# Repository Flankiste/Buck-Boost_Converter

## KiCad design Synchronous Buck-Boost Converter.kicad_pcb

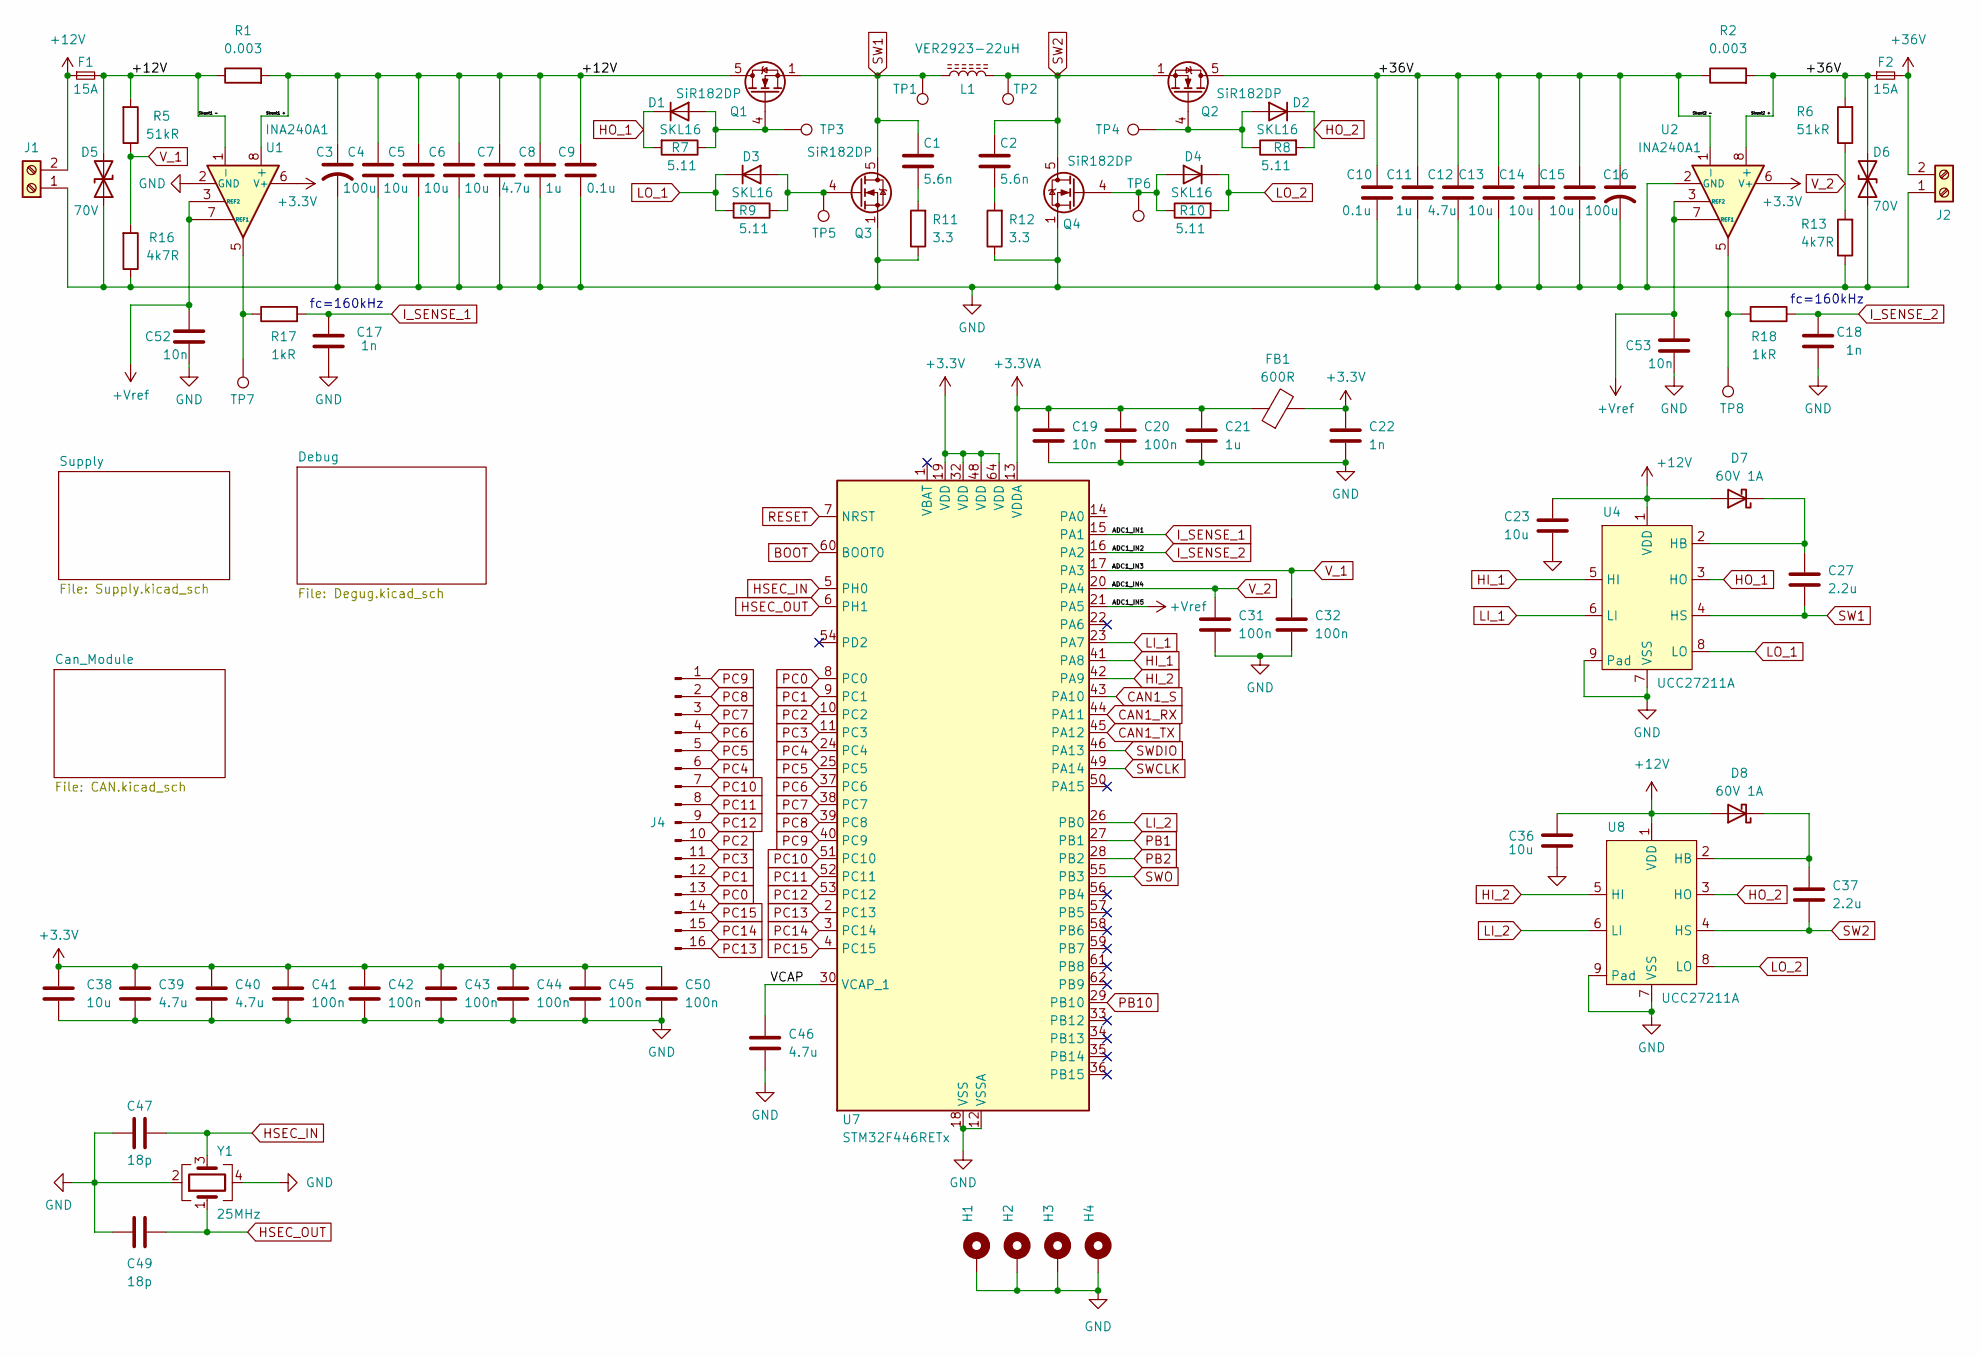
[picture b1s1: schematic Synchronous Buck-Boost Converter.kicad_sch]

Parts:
C1, C2: 5.6n; C_1206_3216Metric
C3, C16: 100u; C_Elec_10x10.2
C4, C5, C6, C13, C14, C15, C23, C36, C38: 10u; C_1210_3225Metric
C7, C12: 4.7u; C_1210_3225Metric
C8, C11: 1u; C_1206_3216Metric
C9, C10: 0.1u; C_0603_1608Metric
C17, C18, C22: 1n; C_0603_1608Metric
C19, C52, C53: 10n; C_0603_1608Metric
C20, C31, C32, C41, C42, C43, C44, C45, C50: 100n; C_0805_2012Metric
C21: 1u; C_0805_2012Metric
C27, C37: 2.2u; C_0805_2012Metric
C39, C40, C46: 4.7u; C_0805_2012Metric
C47, C49: 18p; C_0402_1005Metric
D1, D2, D3, D4: SKL16; Nexperia_CFP3_SOD-123W
D5, D6: 70V; D_SMA
D7, D8: 60V 1A; D_MicroSMP_AK
F1, F2: 15A; Fuse_2512_6332Metric_Pad1.52x3.35mm_HandSolder
FB1: 600R; L_0603_1608Metric
H1, H2, H3, H4: MountingHole_Pad; MountingHole_4.3mm_M4_Pad_Via
J1, J2: Screw_Terminal_01x02; TerminalBlock_Phoenix_MKDS-1,5-2-5.08_1x02_P5.08mm_Horizont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
J4: Conn_01x16_Pin; PinHeader_1x16_P2.54mm_Vertical
L1: VER2923-22uH; VER2923
Q1, Q2, Q3, Q4: SiR182DP; PowerPAK_SO-8_Single
R1, R2: 0.003; R_2512_6332Metric
R5, R6: 51kR; R_0805_2012Metric
R7, R8, R9, R10: 5.11; R_0805_2012Metric
R11, R12: 3.3; R_2512_6332Metric
R13, R16: 4k7R; R_0805_2012Metric
R17, R18: 1kR; R_0805_2012Metric_Pad1.20x1.40mm_HandSolder
TP1, TP2, TP3, TP4, TP5, TP6, TP7, TP8: TestPoint_Pad_D1.5mm
U1, U2: INA240A1; SOIC-8_3.9x4.9mm_P1.27mm
U4, U8: UCC27211A; TI_SO-PowerPAD-8
U7: STM32F446RETx; LQFP-64_10x10mm_P0.5mm
Y1: 25MHz; Crystal_SMD_3225-4Pin_3.2x2.5mm

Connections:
+3.3V: C22.1, C38.1, C39.1, C40.1, C41.1, C42.1, C43.1, C44.1, C45.1, C50.1, FB1.2, U1.6 (V+), U2.6 (V+), U7.19 (VDD), U7.32 (VDD), U7.48 (VDD), U7.64 (VDD); also elsewhere on the board
+3.3VA: C19.1, C20.1, C21.1, FB1.1, U7.13 (VDDA)
+12V: C3.1, C4.2, C5.2, C6.2, C7.2, C8.2, C9.2, C23.1, C36.1, D5.2 (A2), D7.2 (A), D8.2 (A), F1.1, F1.2, J1.2, Q1.5 (D), R1.1, R1.2, R5.2, U1.1 (-), U1.8 (+), U4.1 (VDD), U8.1 (VDD); also elsewhere on the board
+36V: C10.1, C11.1, C12.1, C13.1, C14.1, C15.1, C16.1, D6.2 (A2), F2.1, F2.2, J2.2, Q2.5 (D), R2.1, R2.2, R6.2, U2.1 (-), U2.8 (+)
+Vref: C52.1, C53.1, U1.3 (REF2), U1.7 (REF1), U2.3 (REF2), U2.7 (REF1), U7.21 (PA5); also elsewhere on the board
/VCAP: C46.1, U7.30 (VCAP_1)
BOOT: U7.60 (BOOT0); also elsewhere on the board
CAN1_RX: U7.44 (PA11); also elsewhere on the board
CAN1_S: U7.43 (PA10); also elsewhere on the board
CAN1_TX: U7.45 (PA12); also elsewhere on the board
GND: C3.2, C4.1, C5.1, C6.1, C7.1, C8.1, C9.1, C10.2, C11.2, C12.2, C13.2, C14.2, C15.2, C16.2, C17.2, C18.2, C19.2, C20.2, C21.2, C22.2, C23.2, C31.2, C32.2, C36.2, C38.2, C39.2, C40.2, C41.2, C42.2, C43.2, C44.2, C45.2, C46.2, C47.1, C49.1, C50.2, C52.2, C53.2, D5.1 (A1), D6.1 (A1), H1.1, H2.1, H3.1, H4.1, J1.1, J2.1, Q3.1 (S), Q3.2 (S), Q3.3 (S), Q4.1 (S), Q4.2 (S), Q4.3 (S), R11.1, R12.1, R13.1, R16.1, U1.2 (GND), U1.4 (GND), U2.2 (GND), U2.4 (GND), U4.7 (VSS), U4.9 (Pad), U7.12 (VSSA), U7.18 (VSS), U7.31 (VSS), U7.47 (VSS), U7.63 (VSS), U8.7 (VSS), U8.9 (Pad), Y1.2, Y1.4; also elsewhere on the board
HI_1: U4.5 (HI), U7.41 (PA8)
HI_2: U7.42 (PA9), U8.5 (HI)
HO_1: D1.1 (K), R7.2, U4.3 (HO)
HO_2: D2.1 (K), R8.2, U8.3 (HO)
HSEC_IN: C47.2, U7.5 (PH0), Y1.3
HSEC_OUT: C49.2, U7.6 (PH1), Y1.1
I_SENSE_1: C17.1, R17.2, U7.15 (PA1)
I_SENSE_2: C18.1, R18.1, U7.16 (PA2)
LI_1: U4.6 (LI), U7.23 (PA7)
LI_2: U7.26 (PB0), U8.6 (LI)
LO_1: D3.1 (K), R9.2, U4.8 (LO)
LO_2: D4.1 (K), R10.2, U8.8 (LO)
unnamed: C1.2, R11.2
unnamed: C2.2, R12.2
unnamed: D1.2 (A), Q1.4 (G), R7.1, TP3.1
unnamed: D2.2 (A), Q2.4 (G), R8.1, TP4.1
unnamed: D3.2 (A), Q3.4 (G), R9.1, TP5.1
unnamed: D4.2 (A), Q4.4 (G), R10.1, TP6.1
unnamed: R17.1, TP7.1, U1.5
unnamed: R18.2, TP8.1, U2.5
unnamed: C27.1, D7.1 (K), U4.2 (HB)
unnamed: C37.1, D8.1 (K), U8.2 (HB)
PB1: U7.27 (PB1); also elsewhere on the board
PB2: U7.28 (PB2); also elsewhere on the board
PB10: U7.29 (PB10); also elsewhere on the board
PC0: J4.13, U7.8 (PC0)
PC1: J4.12, U7.9 (PC1)
PC2: J4.10, U7.10 (PC2)
PC3: J4.11, U7.11 (PC3)
PC4: J4.6, U7.24 (PC4)
PC5: J4.5, U7.25 (PC5)
PC6: J4.4, U7.37 (PC6)
PC7: J4.3, U7.38 (PC7)
PC8: J4.2, U7.39 (PC8)
PC9: J4.1, U7.40 (PC9)
PC10: J4.7, U7.51 (PC10)
PC11: J4.8, U7.52 (PC11)
PC12: J4.9, U7.53 (PC12)
PC13: J4.16, U7.2 (PC13)
PC14: J4.15, U7.3 (PC14)
PC15: J4.14, U7.4 (PC15)
RESET: U7.7 (NRST); also elsewhere on the board
SW1: C1.1, C27.2, L1.1, Q1.1 (S), Q1.2 (S), Q1.3 (S), Q3.5 (D), TP1.1, U4.4 (HS)
SW2: C2.1, C37.2, L1.2, Q2.1 (S), Q2.2 (S), Q2.3 (S), Q4.5 (D), TP2.1, U8.4 (HS)
SWCLK: U7.49 (PA14); also elsewhere on the board
SWDIO: U7.46 (PA13); also elsewhere on the board
SWO: U7.55 (PB3); also elsewhere on the board
V_1: C32.1, R5.1, R16.2, U7.17 (PA3)
V_2: C31.1, R6.1, R13.2, U7.20 (PA4)

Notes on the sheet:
fc=160kHz

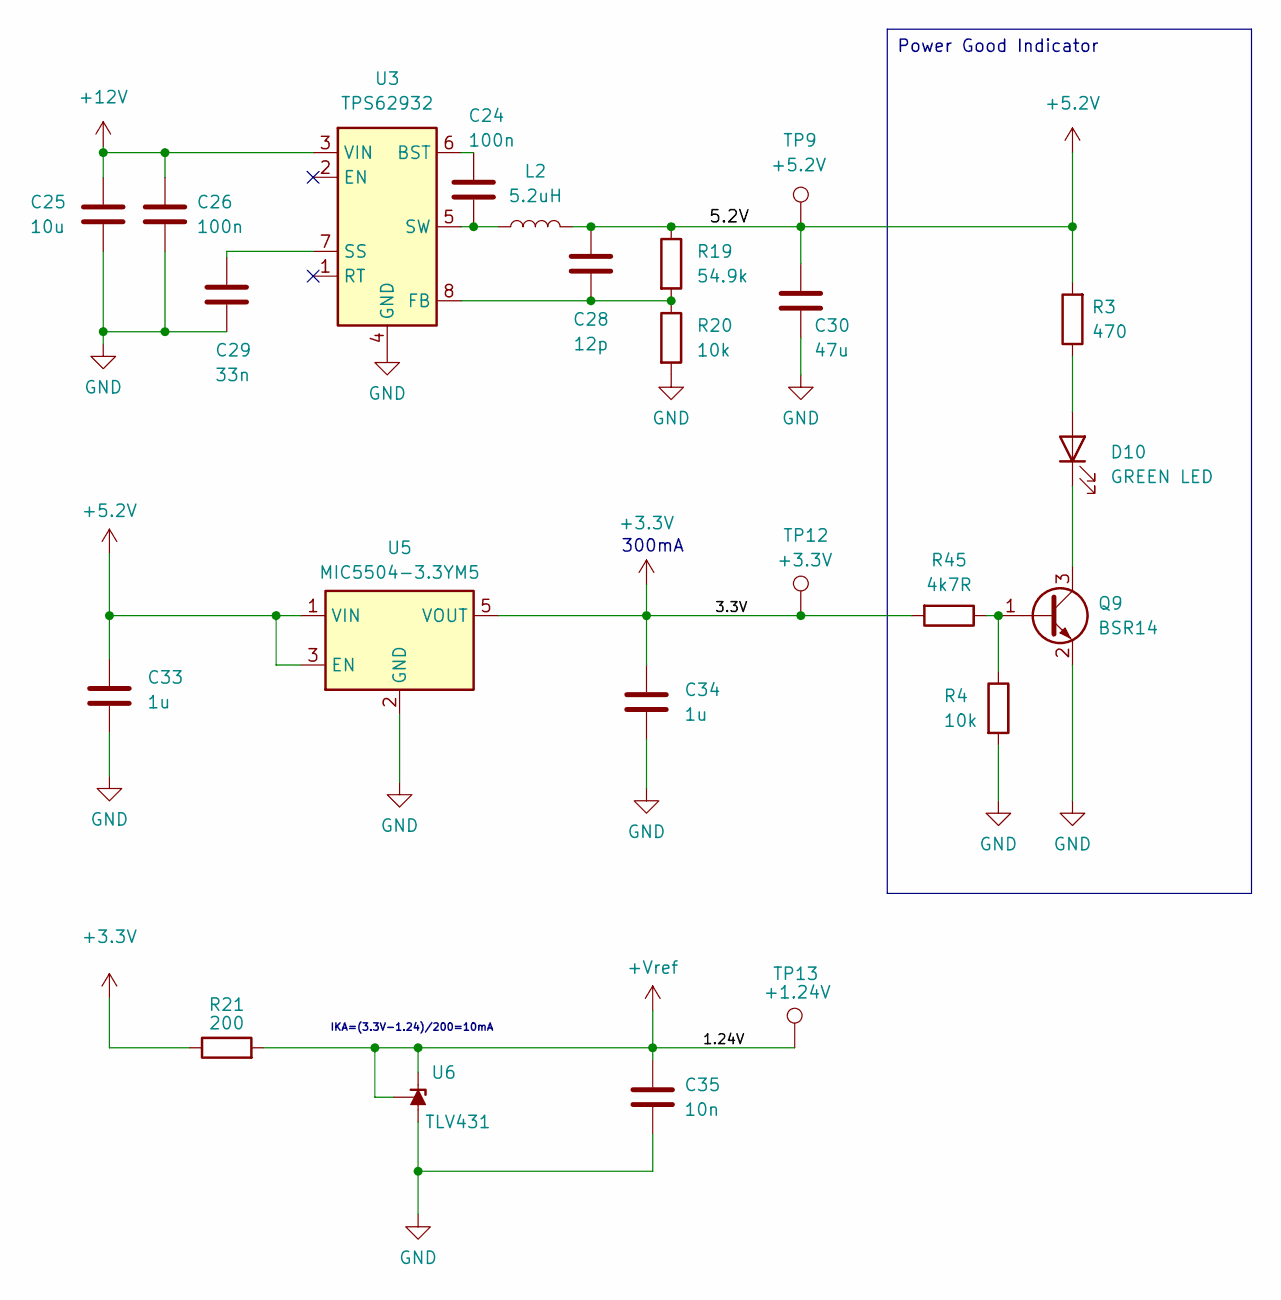
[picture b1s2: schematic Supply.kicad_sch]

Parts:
C24, C26: 100n; C_0805_2012Metric
C25: 10u; C_1210_3225Metric
C28: 12p; C_0603_1608Metric
C29: 33n; C_0603_1608Metric
C30: 47u; C_1210_3225Metric
C33, C34: 1u; C_0805_2012Metric
C35: 10n; C_0603_1608Metric
D10: GREEN LED; LED_0603_1608Metric
L2: 5.2uH; L_Bourns-SRU1038_10.0x10.0mm
Q9: BSR14; SOT-23-3
R3: 470; R_0603_1608Metric
R4, R20: 10k; R_0603_1608Metric
R19: 54.9k; R_0603_1608Metric
R21: 200; R_0805_2012Metric
R45: 4k7R; R_0805_2012Metric
TP9: +5.2V; TestPoint_Pad_D1.5mm
TP12: +3.3V; TestPoint_Pad_D1.5mm
TP13: +1.24V; TestPoint_Pad_D1.5mm
U3: TPS62932; SOT-583-8
U5: MIC5504-3.3YM5; SOT-23-5
U6: TLV431; SOT-23

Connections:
+3.3V: C34.1, R21.1, R45.2, TP12.1, U5.5 (VOUT); also elsewhere on the board
+5.2V: C28.2, C30.1, C33.1, L2.2, R3.2, R19.1, TP9.1, U5.1 (VIN), U5.3 (EN); also elsewhere on the board
+12V: C25.1, C26.1, U3.3 (VIN); also elsewhere on the board
+Vref: C35.1, R21.2, TP13.1, U6.1 (REF), U6.2 (K); also elsewhere on the board
GND: C25.2, C26.2, C29.2, C30.2, C33.2, C34.2, C35.2, Q9.2 (E), R4.2, R20.2, U3.4 (GND), U5.2 (GND), U6.3 (A); also elsewhere on the board
unnamed: D10.2 (A), R3.1
unnamed: D10.1 (K), Q9.3 (C)
unnamed: Q9.1 (B), R4.1, R45.1
unnamed: C24.1, U3.6 (BST)
unnamed: C28.1, R19.2, R20.1, U3.8 (FB)
unnamed: C29.1, U3.7 (SS)
unnamed: C24.2, L2.1, U3.5 (SW)

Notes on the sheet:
IKA=(3.3V-1.24)/200=10mA
300mA
Power Good Indicator

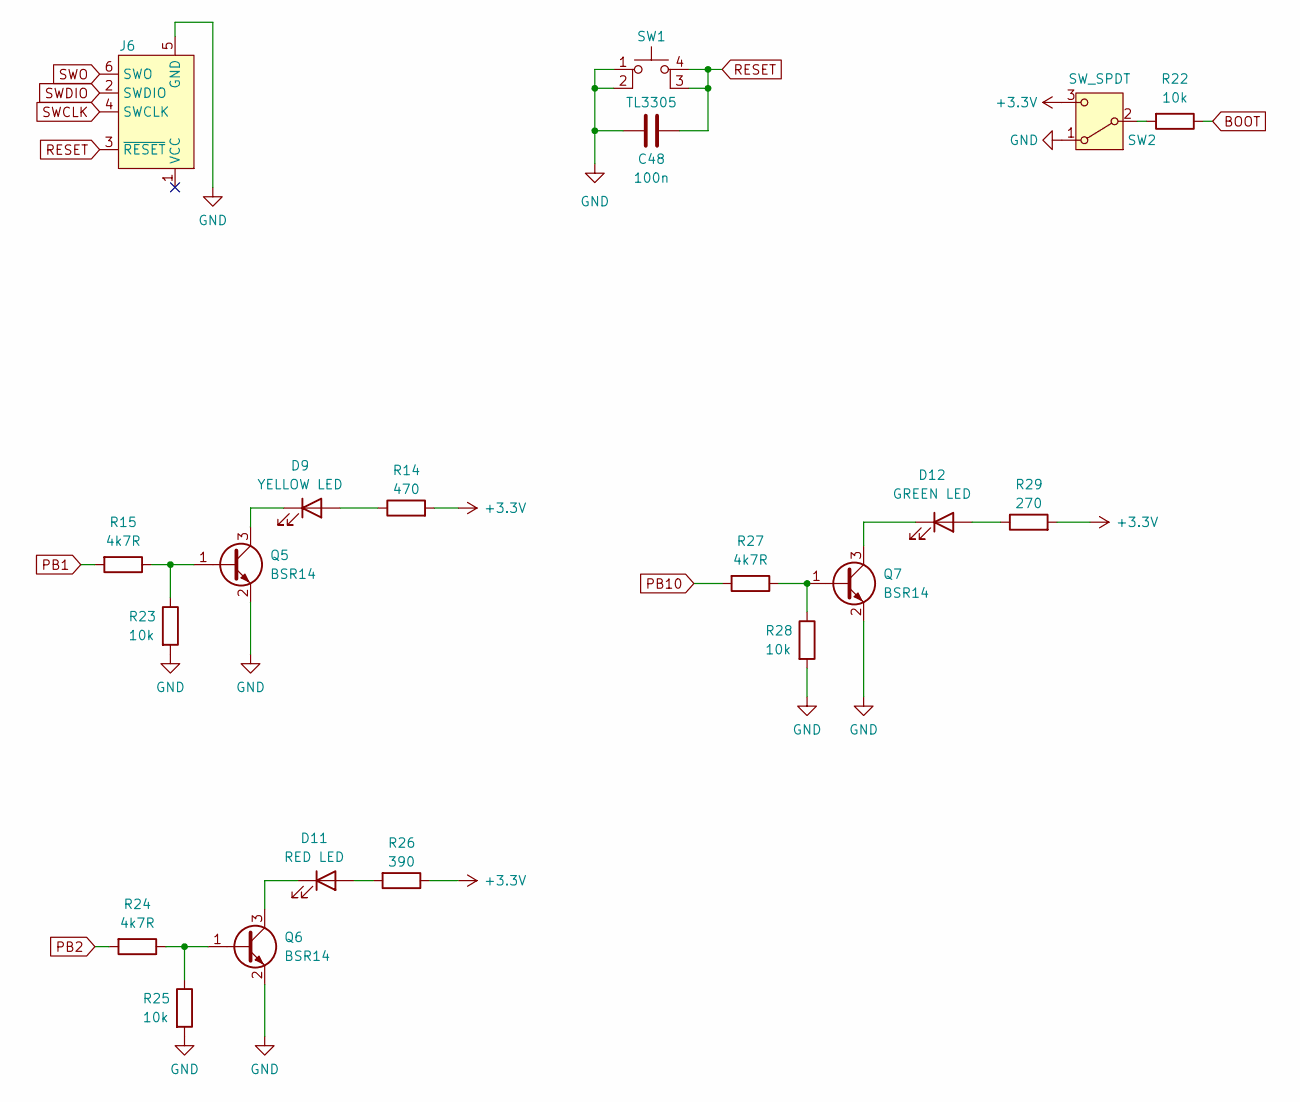
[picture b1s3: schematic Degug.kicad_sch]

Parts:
C48: 100n; C_0805_2012Metric
D9: YELLOW LED; LED_0603_1608Metric
D11: RED LED; LED_0603_1608Metric
D12: GREEN LED; LED_0603_1608Metric
J6: Conn_ARM_SWD_TagConnect_TC2030-NL; Tag-Connect_TC2030-IDC-NL_2x03_P1.27mm_Vertical
Q5, Q6, Q7: BSR14; SOT-23-3
R14: 470; R_0603_1608Metric
R15, R24, R27: 4k7R; R_0805_2012Metric
R22, R23, R25, R28: 10k; R_0603_1608Metric
R26: 390; R_0603_1608Metric
R29: 270; R_0603_1608Metric
SW1: TL3305
SW2: SW_SPDT; SW_SPDT_PCM12

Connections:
+3.3V: R14.2, R26.1, R29.2, SW2.3 (C); also elsewhere on the board
BOOT: R22.1; also elsewhere on the board
GND: C48.1, J6.5 (GND), Q5.2 (E), Q6.2 (E), Q7.2 (E), R23.2, R25.2, R28.2, SW1.1, SW1.2, SW2.1 (A); also elsewhere on the board
unnamed: D9.2 (A), R14.1
unnamed: D9.1 (K), Q5.3 (C)
unnamed: D11.2 (A), R26.2
unnamed: D11.1 (K), Q6.3 (C)
unnamed: D12.2 (A), R29.1
unnamed: D12.1 (K), Q7.3 (C)
unnamed: Q5.1 (B), R15.1, R23.1
unnamed: Q6.1 (B), R24.1, R25.1
unnamed: Q7.1 (B), R27.1, R28.1
unnamed: R22.2, SW2.2 (B)
PB1: R15.2; also elsewhere on the board
PB2: R24.2; also elsewhere on the board
PB10: R27.2; also elsewhere on the board
RESET: C48.2, J6.3 (~RESET), SW1.3 (K), SW1.4 (A); also elsewhere on the board
SWCLK: J6.4 (SWCLK); also elsewhere on the board
SWDIO: J6.2 (SWDIO); also elsewhere on the board
SWO: J6.6 (SWO); also elsewhere on the board

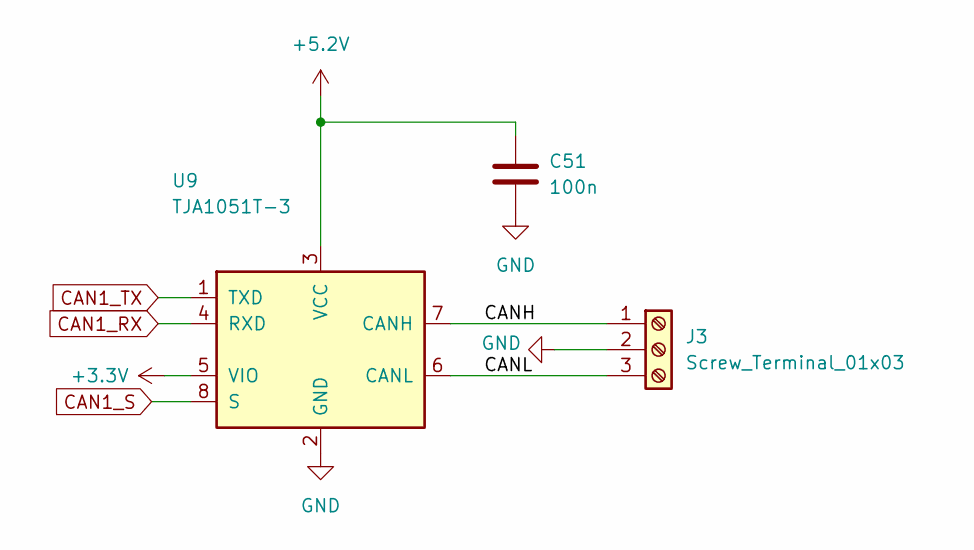
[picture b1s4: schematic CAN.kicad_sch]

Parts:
C51: 100n; C_0805_2012Metric
J3: Screw_Terminal_01x03; TerminalBlock_Phoenix_PT-1,5-3-3.5-H_1x03_P3.50mm_Horizontal
U9: TJA1051T-3; SOIC-8_3.9x4.9mm_P1.27mm

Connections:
+3.3V: U9.5 (VIO); also elsewhere on the board
+5.2V: C51.1, U9.3 (VCC); also elsewhere on the board
/Can_Module/CANH: J3.1, U9.7 (CANH)
/Can_Module/CANL: J3.3, U9.6 (CANL)
CAN1_RX: U9.4 (RXD); also elsewhere on the board
CAN1_S: U9.8 (S); also elsewhere on the board
CAN1_TX: U9.1 (TXD); also elsewhere on the board
GND: C51.2, J3.2, U9.2 (GND); also elsewhere on the board

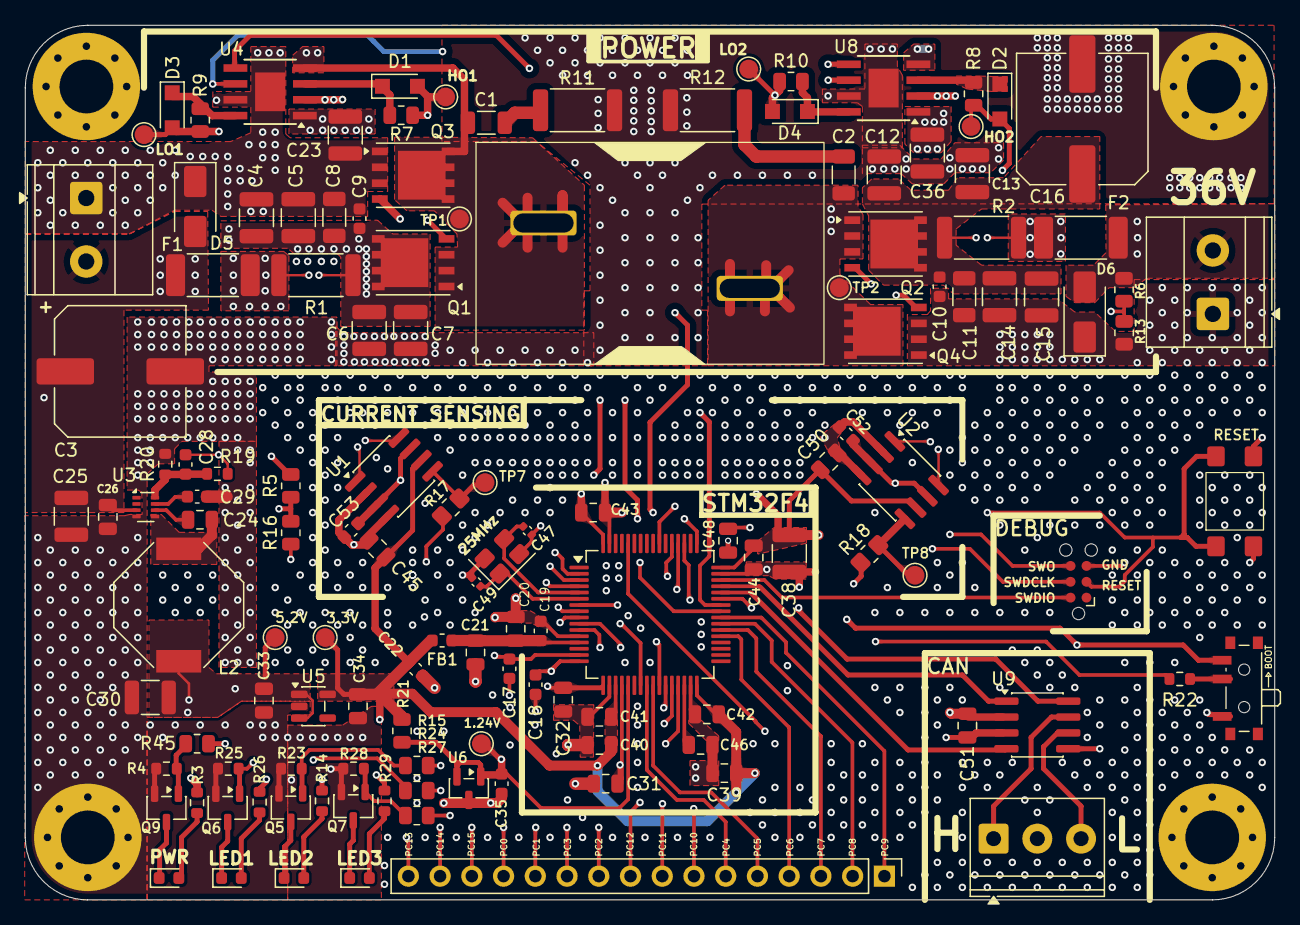
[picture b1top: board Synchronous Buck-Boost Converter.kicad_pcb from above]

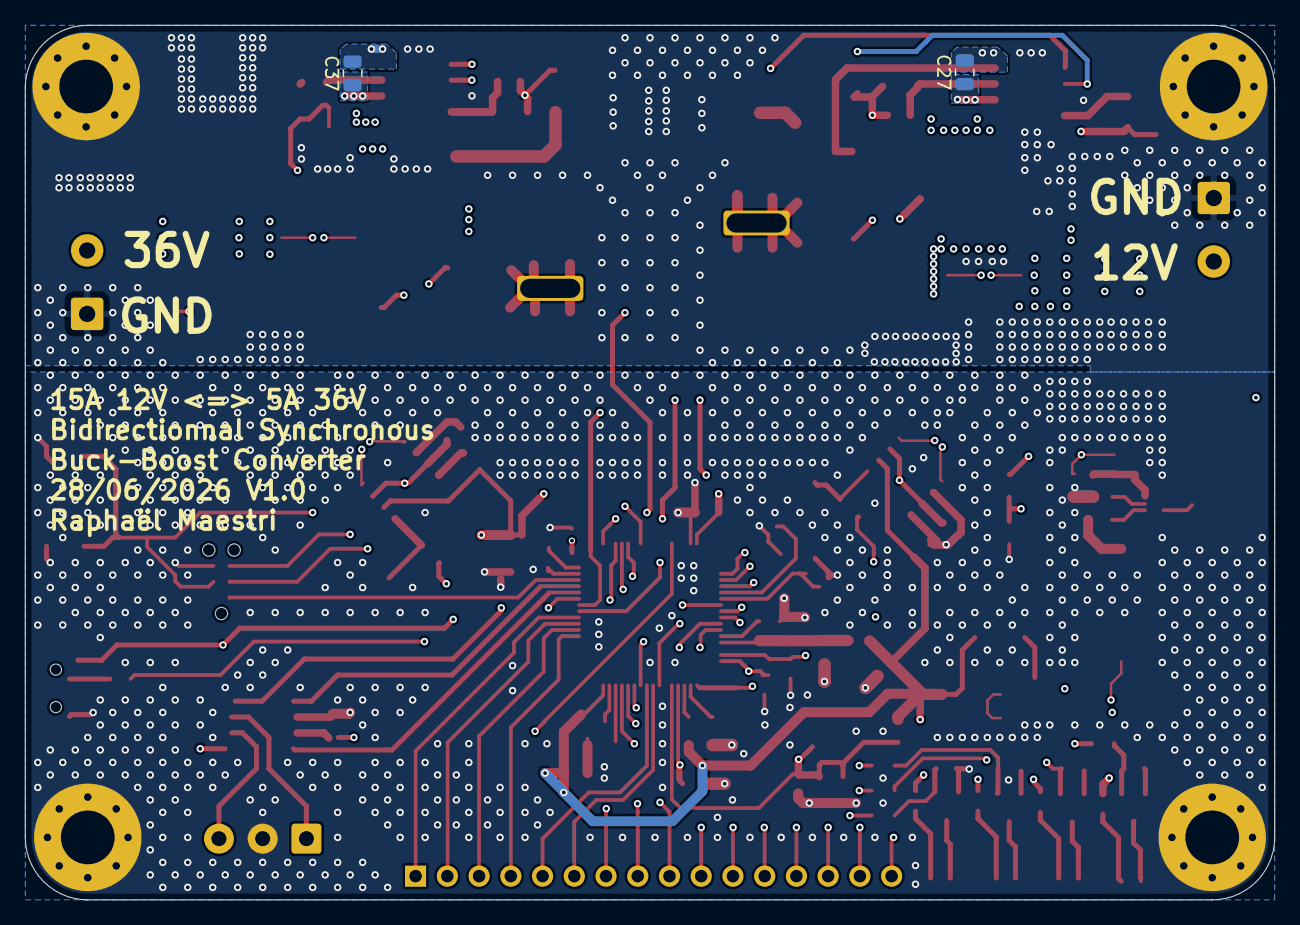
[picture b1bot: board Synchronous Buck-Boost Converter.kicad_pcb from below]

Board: 4 copper layers, 100.0 x 70.0 mm, 138 parts (2 on the bottom side), 80 nets.

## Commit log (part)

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2026-02-10 Testing pcb fab
